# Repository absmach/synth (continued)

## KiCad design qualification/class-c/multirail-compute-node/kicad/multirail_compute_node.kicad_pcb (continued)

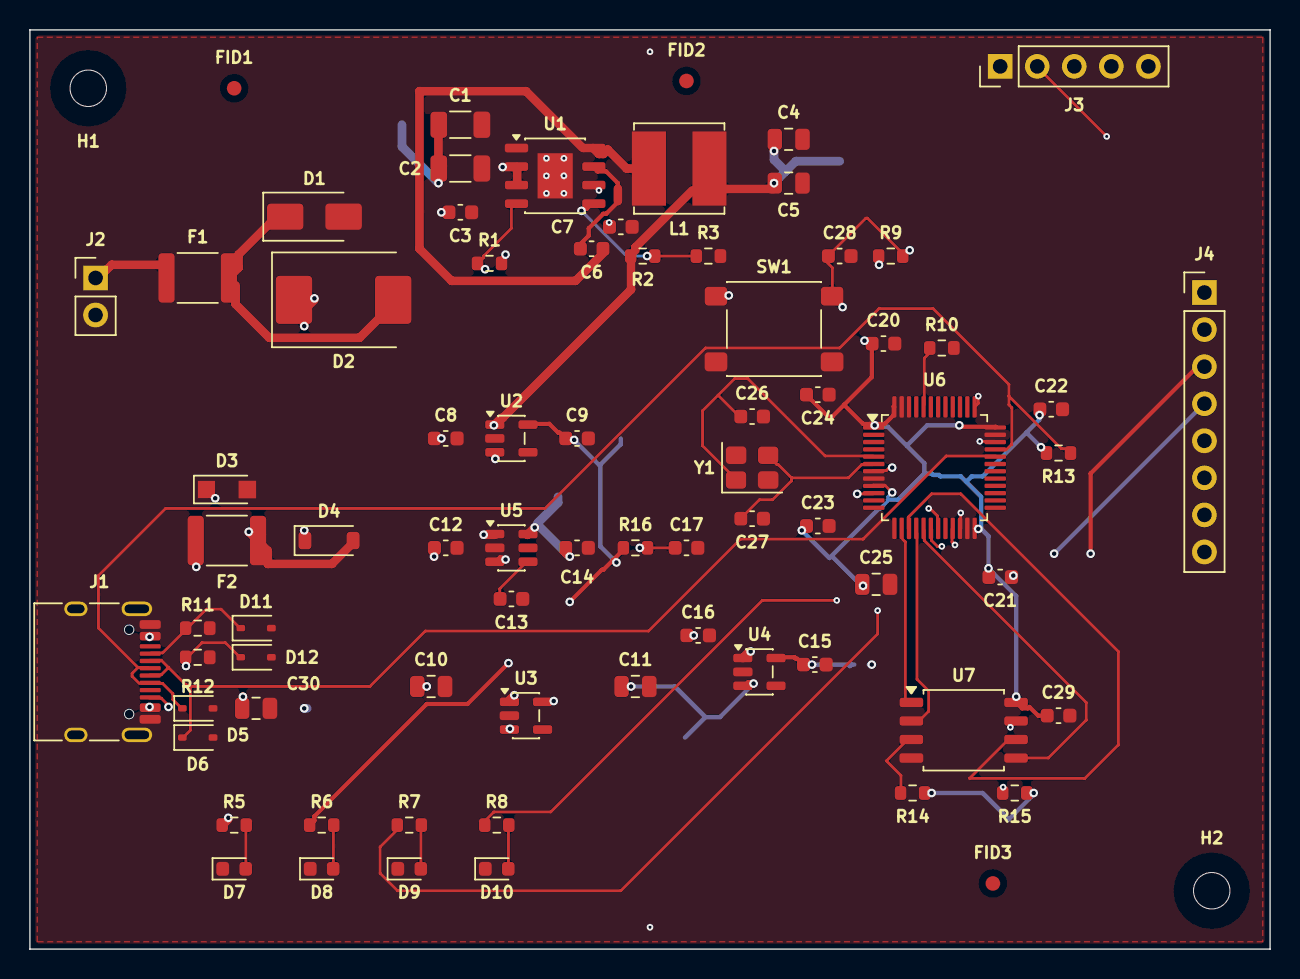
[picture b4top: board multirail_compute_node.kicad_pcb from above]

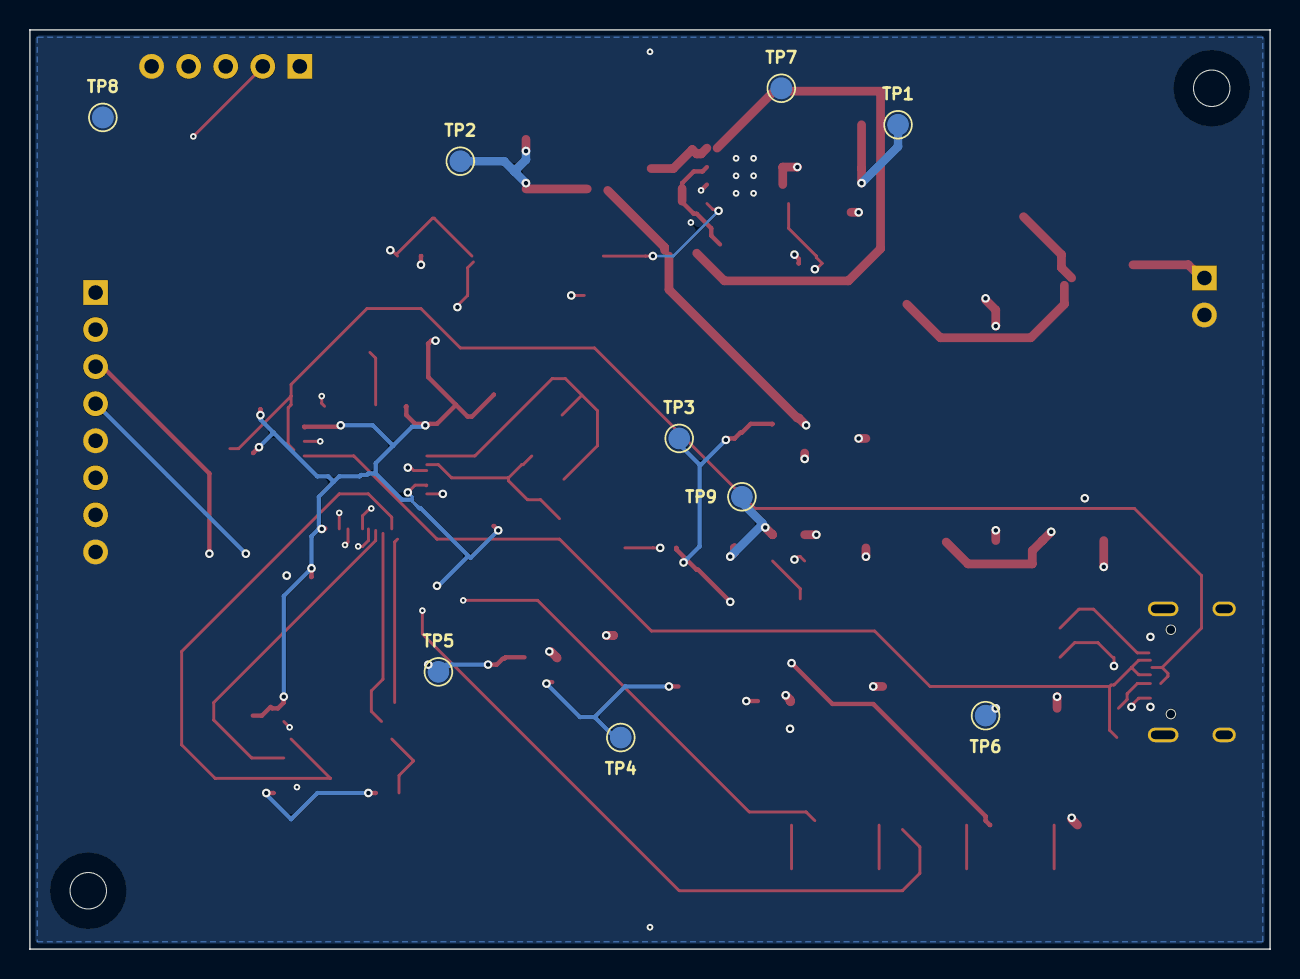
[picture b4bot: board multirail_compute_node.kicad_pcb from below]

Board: 4 copper layers, 85.0 x 63.0 mm, 85 parts (9 on the bottom side), 42 nets.

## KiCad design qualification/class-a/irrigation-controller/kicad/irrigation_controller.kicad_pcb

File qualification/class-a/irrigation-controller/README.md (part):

# Irrigation controller (Class A, case 1)

A two-zone irrigation controller powered from 12 V DC. It has an input fuse, a TVS, an ideal-diode reverse-polarity stage, an MP2307 buck to 3.3 V, an STM32G030 microcontroller, two low-side solenoid drivers, two soil probes with AC excitation, a flow-pulse input and an I2C header with an ambient light sensor and an EEPROM. The board has two copper layers, uses the JLCPCB process and measures 79.2 x 70.7 mm.

The board answers case 1 of the Class A qualification set: a mixed power, MCU and field-wiring design. It claims only what the tables below show from the board files, the measured KiCad checks and the cited datasheets. No figure is measured on hardware.

The prompt to reproduce the board is in [`PROMPT.md`](PROMPT.md), written from the finished board. The prompts the agent ran are in the history at `e0e004eb`.

## The board

### Parts

| Group                     | Parts                                                                                                                                                                                                                                                                                                      |
| ------------------------- | ---------------------------------------------------------------------------------------------------------------------------------------------------------------------------------------------------------------------------------------------------------------------------------------------------------- |
| Power input               | `J1` JST XH 2-pin supply connector; `F1` Littelfuse 1812L150/16DR resettable fuse (1.5 A hold); `D_TVS` SMAJ13A (13.0 V standoff, 21.5 V clamp at 18.6 A)                                                                                                                                                  |
| Ideal-diode stage         | `U_IDEAL` Texas Instruments LM74700-Q1 (SOT-23-6) driving `Q1` Diodes DMT6007LFG (60 V, 8.5 mOhm maximum at 4.5 V gate drive); `C_VCAP` and `C_VIN` (100 nF each) at the controller; `C_BULK` (100 uF) on the output                                                                                       |
| 3.3 V buck                | `U1` MPS MP2307DN; input capacitors `C_IN1` and `C_IN2` (10 uF); inductor `L1` Bourns SRN6045TA-100M (10 uH); output capacitors `C_OUT1` and `C_OUT2` (22 uF); feedback divider `R_FBT` 26.1 k and `R_FBB` 10 k; compensation `R_COMP` 5.6 k and `C_COMP` 4.7 nF; soft-start `C_SS`; enable divider `R_EN` |
| MCU                       | `U2` STMicroelectronics STM32G030K8T6 (LQFP-32); supply capacitors `C_VDD1` and `C_VDD2`; reset network `R_NRST`, `C_NRST` and the tactile switch `SW_RESET`; 5-pin SWD header `J_SWD`                                                                                                                     |
| MCU clock                 | 32.768 kHz LSE crystal `Y1` Epson FC-135 32.7680KF-AG0 (7 pF load) with `C_X1` and `C_X2` (4.3 pF); HSI16 is the system clock, because the LQFP-32 has no HSE crystal oscillator                                                                                                                           |
| Valves 1 and 2            | Per valve: a JST XH 2-pin connector (`J_VALVE1`, `J_VALVE2`); a low-side AO3400A N-MOSFET (`Q_V1`, `Q_V2`) with a 100 ohm gate resistor and a 100 k pull-down; a 1N5819HW flyback diode (`D_FLY1`, `D_FLY2`); an RC snubber (100 ohm, 10 nF)                                                               |
| Valve short-circuit sense | Per valve: a 0.1 ohm shunt (`R_SH1`, `R_SH2`) in the MOSFET source, read on `PA1` and `PA0` through 1 k and 10 nF (`R_IS`, `C_IS`)                                                                                                                                                                         |
| Soil probes 1 and 2       | Per probe: a JST PH 3-pin connector (`J_SOIL1`, `J_SOIL2`); AC excitation from two GPIOs through 10 k resistors (`R_S1`, `R_D1`, `R_S2`, `R_D2`); both probe nodes sampled through 1 k and 10 nF filters                                                                                                   |
| Flow input                | `J_FLOW` JST PH 3-pin; pull-up `R_FPU`; series resistor `R_FS`; 3.3 V zener `D_FZ` that clamps the pulse input; filter `C_FL`                                                                                                                                                                              |
| I2C                       | `J_I2C` JST PH 4-pin; 4.7 k pull-ups `R_SDA` and `R_SCL`; `U4` Broadcom APDS-9301 ambient light sensor and `U5` Microchip 24LC256 EEPROM, each with a 100 nF capacitor                                                                                                                                     |
| Humidity sensor           | None on the board. A breakout attaches to the I2C header at address 0x44.                                                                                                                                                                                                                                  |
| Field-wiring protection   | PRTR5V0U2X ESD arrays at the soil and I2C connectors (`D_ESD_S1`, `D_ESD_S2`, `D_ESD_I2C`); SMAJ15A TVS on the flow input (`D_ESD_FL`)                                                                                                                                                                     |
| Indicators                | `D_PWR` green (Lite-On LTST-C190KGKT); `D_VALVE` and `D_N1` amber (KENTO KT-0603Y); each with a series resistor                                                                                                                                                                                            |
| Test points               | `TP_VIN`, `TP_12V`, `TP_3V3`, `TP_GND`, `TP_NRST`, `TP_SWDIO`, `TP_SWCLK`, `TP_SDA`, `TP_SCL`, `TP_FLOW`, `TP_SOIL1`, `TP_SOIL2`, `TP_V1`, `TP_V2`, `TP_N1`, `TP_N2`, all on the bottom side of the board |
| Mechanical                | Four M2.5 mounting holes `H1` to `H4`, one in each corner, each 4.0 mm from its two board edges                                                                                                                                                                                                                                                  |

### Layout

| Item                    | Value                                                                                                                                                                                                     |
| ----------------------- | --------------------------------------------------------------------------------------------------------------------------------------------------------------------------------------------------------- |
| Outline                 | 79.2 x 70.7 mm                                                                                                                                                                                            |
| Copper layers           | 2                                                                                                                                                                                                         |
| Stackup                 | 1.6 mm board thickness; JLCPCB process; no layer stackup is defined in the board file                                                                                                                     |
| Parts in the BOM        | 107 lines: 87 parts and 20 board features (4 mounting holes, 16 test points)                                                                                                                              |
| Parts placed in the CPL | 87                                                                                                                                                                                                        |
| Nets                    | 51                                                                                                                                                                                                        |
| Track segments          | 629                                                                                                                                                                                                       |
| Vias                    | 117: 1 of 0.46/0.2 mm, 109 of 0.6/0.2 mm and 7 of 0.6/0.3 mm                                                                                                                                                                                                       |
| Track length            | 1644.7 mm                                                                                                                                                                                                 |
| Zones and planes        | GND pour on F.Cu and on B.Cu; four keepout zones at the screw heads of `H1` to `H4` on both layers                                                                                                        |
| Fab package             | `fab/gerbers.zip` (copper, mask, paste, silkscreen, edge cuts, PTH and NPTH drill files and maps, job file), `fab/bom.csv`, `fab/cpl.csv`; STEP model in `models/`; images and schematic PDF in `images/` |
| 3D models               | `models/` holds the STEP body of every part the board references and the board model `irrigation_controller.step`. The board file reaches them by the relative path `${KIPRJMOD}/../models/`. Mounting holes and fiducials have no body. A part that KiCad's library has no model for is a simplified box of its envelope. |
| Schematic               | `images/schematic.pdf`: vector pages, one per sheet, plotted by `kicad-cli sch export pdf`. |

### Checks

| Check                              | Result                               | Notes                                                                                         |
| ---------------------------------- | ------------------------------------ | --------------------------------------------------------------------------------------------- |
| KiCad DRC (10.0.8, --refill-zones) | 0 errors, 0 unconnected, 7 warnings  | 6 `silk_over_copper`, 1 `silk_overlap`                                                        |
| KiCad ERC (10.0.8)                 | 0 errors, 0 unconnected, 28 warnings | 27 `lib_symbol_issues` (library symbol and footprint-link warnings), 1 `label_multiple_wires` |

### Design figures

| Area             | Item                       | Value                                                                                                                                                                                  | Basis                                      |
| ---------------- | -------------------------- | -------------------------------------------------------------------------------------------------------------------------------------------------------------------------------------- | ------------------------------------------ |
| Power            | Supply range               | 12 V +/-5 % (10.8 to 12.6 V)                                                                                                                                                           | Stated design assumption                   |
| Power            | Load budget                | 1.18 A at 12 V: two valves 1.0 A, buck input and flow sensor 0.18 A. 1.25 A at 13.0 V.                                                                                                 | Calculated                                 |
| Power            | Buck compensation          | `R_COMP` 5.6 k and `C_COMP` 4.7 nF put the crossover at 24 kHz (44 uF output) to 34 kHz (about 31 uF after DC-bias derating). This is 0.07 to 0.10 of the 340 kHz switching frequency. | Calculated; MP2307 datasheet               |
| Power            | Ideal-diode capacitors     | `C_VCAP` 100 nF (at least 0.1 uF and 10 x the 2.09 nF Ciss of `Q1`); `C_VIN` 100 nF (at least 22 nF); `C_BULK` 100 uF (at least 100 nF)                                                | LM74700-Q1 and DMT6007LFG datasheets       |
| Power            | `Q1` conduction            | 10 mV drop and 12 mW at 1.18 A                                                                                                                                                         | Calculated from the 8.5 mOhm maximum       |
| Protection       | Surge                      | At most 14 A peak (10/1000 us), 75 % of the SMAJ13A's 18.6 A rating                                                                                                                    | SMAJ13A datasheet; calculated              |
| Protection       | Open-circuit surge covered | 21.5 V + 14 A x R_source: 35.5 V at 1 ohm, 49.5 V at 2 ohm                                                                                                                             | Calculated                                 |
| Protection       | TVS standoff               | 12.6 V is 0.4 V (3.2 %) below the 13.0 V standoff; leakage at most 1 uA there; breakdown 14.40 V minimum at 1 mA                                                                       | SMAJ13A datasheet                          |
| Protection       | Clamp margin, `U1`         | At 21.5 V: 1.5 V below the MP2307's 23 V recommended input; 4.5 V below its 26 V absolute maximum                                                                                      | MP2307 datasheet; calculated               |
| Protection       | Clamp margin, `U_IDEAL`    | At 21.5 V: 43.5 V below its 65 V maximum                                                                                                                                               | LM74700-Q1 datasheet; calculated           |
| Protection       | Clamp margin, `Q1`         | At 21.5 V: 38.5 V below its 60 V rating                                                                                                                                                | DMT6007LFG datasheet; calculated           |
| Protection       | Clamp margin, capacitors   | At 21.5 V: `C_BULK`, `C_IN1`, `C_IN2` are 3.5 V below their 25 V rating                                                                                                                | `fab/bom.csv` ratings; calculated          |
| Protection       | Valve short circuit        | `R_SH1`, `R_SH2` (0.1 ohm, 1 W) give 50 mV at 0.5 A and 0.15 V at the 1.5 A fuse hold. Firmware trips at 0.1 V (1.0 A).                                                                | Calculated                                 |
| Protection       | Flow input clamp           | `D_FZ` 3.3 V zener behind `R_FS` 2.2 k: 4.4 mA and 14 mW at 13.0 V, in a 500 mW part                                                                                                   | Calculated                                 |
| Thermal          | Fuse derating              | `F1` holds 1.5 A at 20 C, 1.25 A at 40 C, 1.10 A at 50 C and 0.60 A at 85 C                                                                                                            | 1812L150/16DR datasheet                    |
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
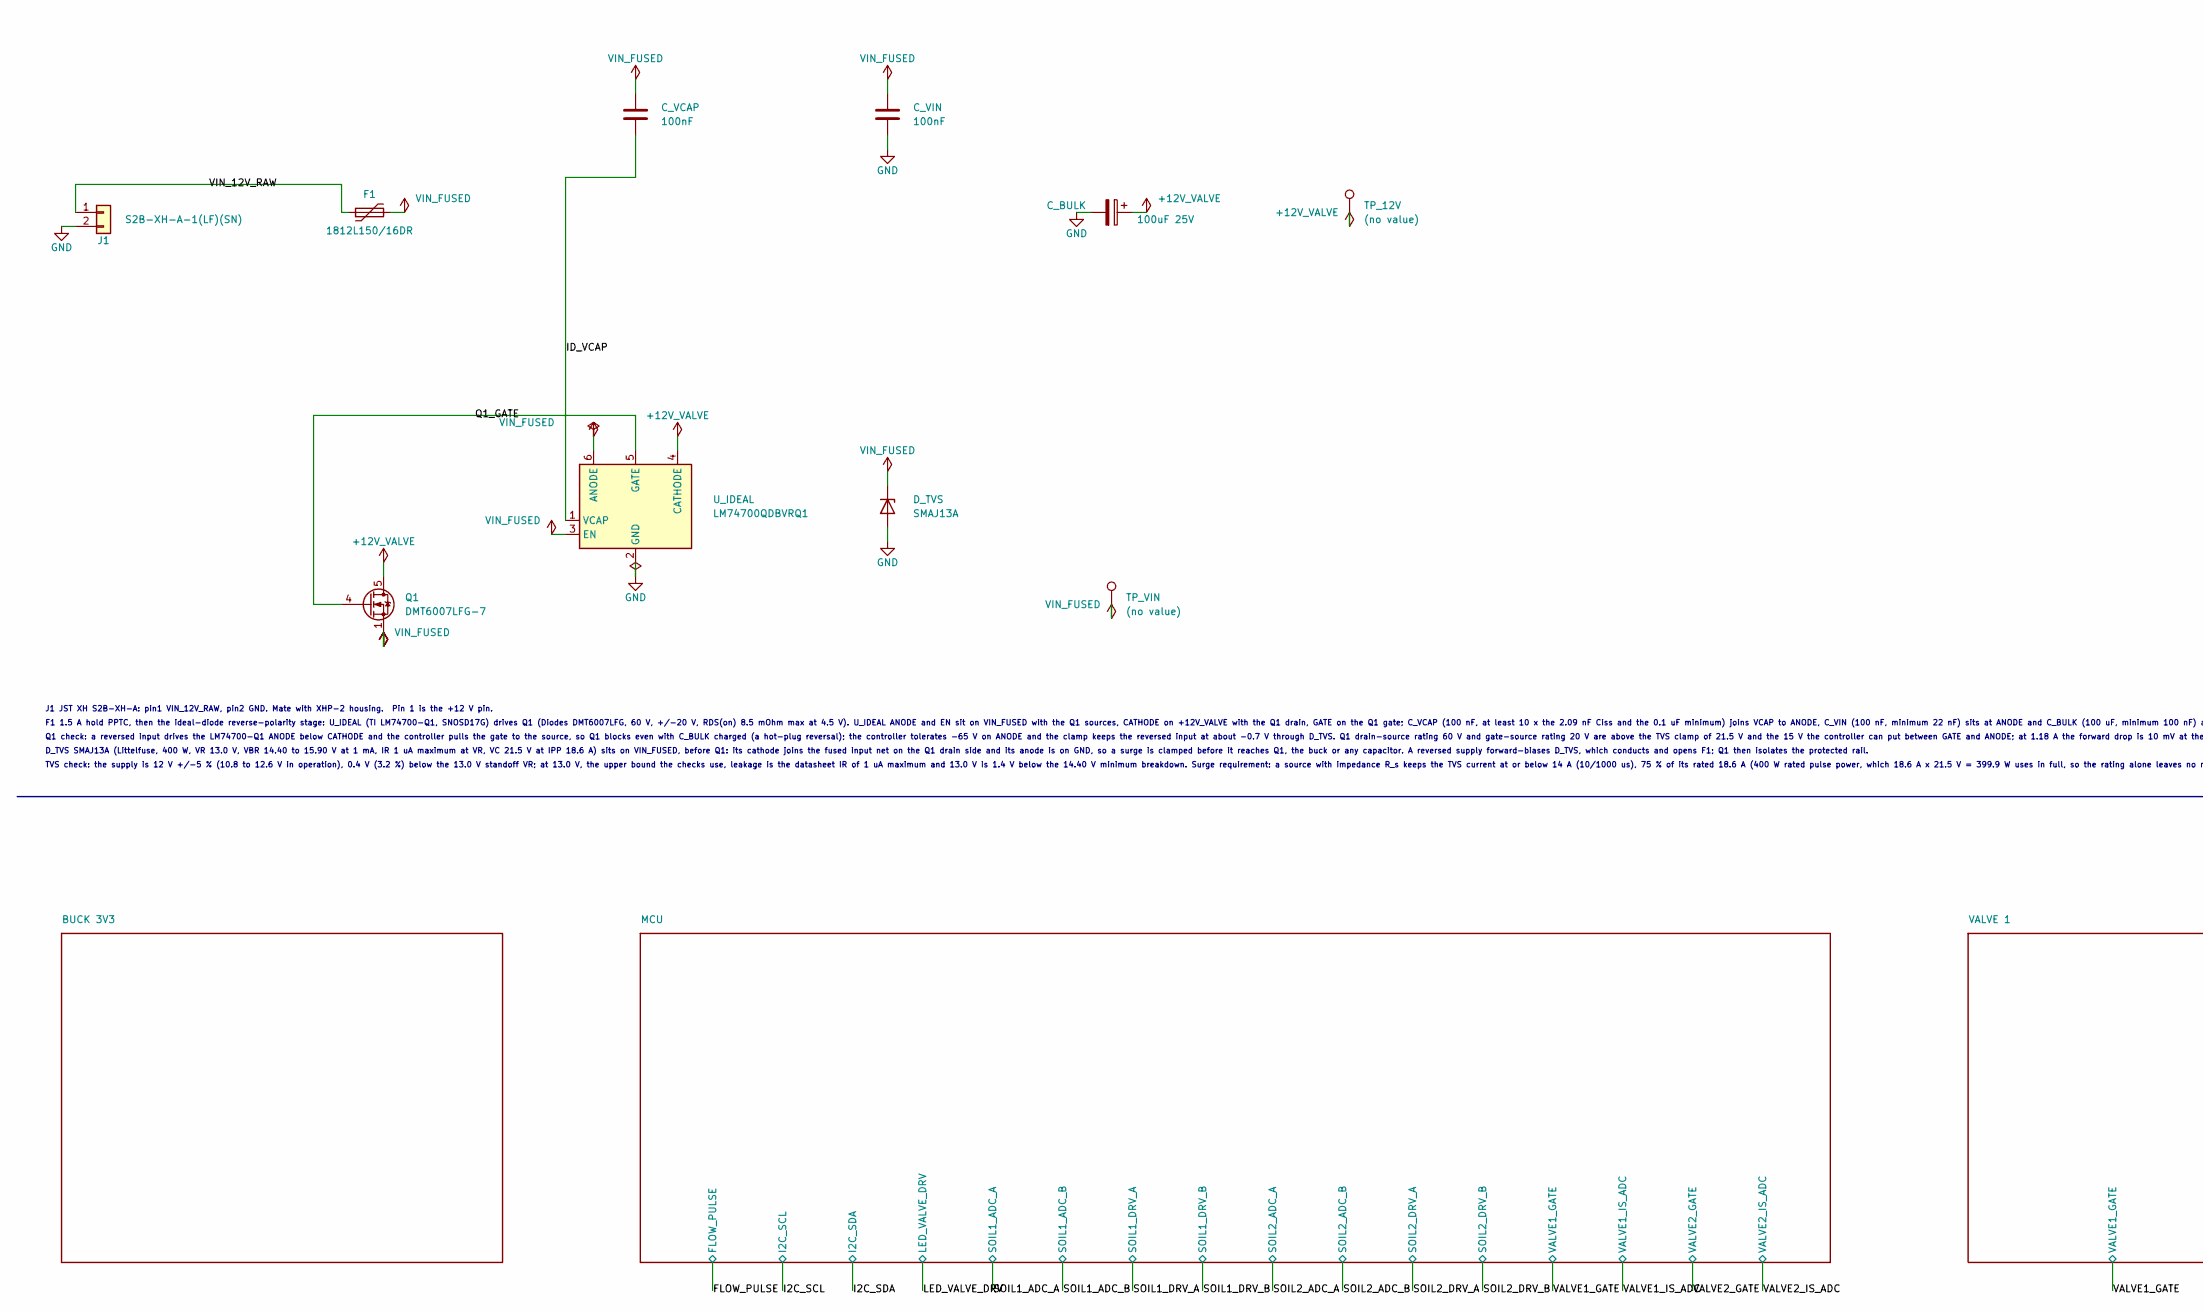
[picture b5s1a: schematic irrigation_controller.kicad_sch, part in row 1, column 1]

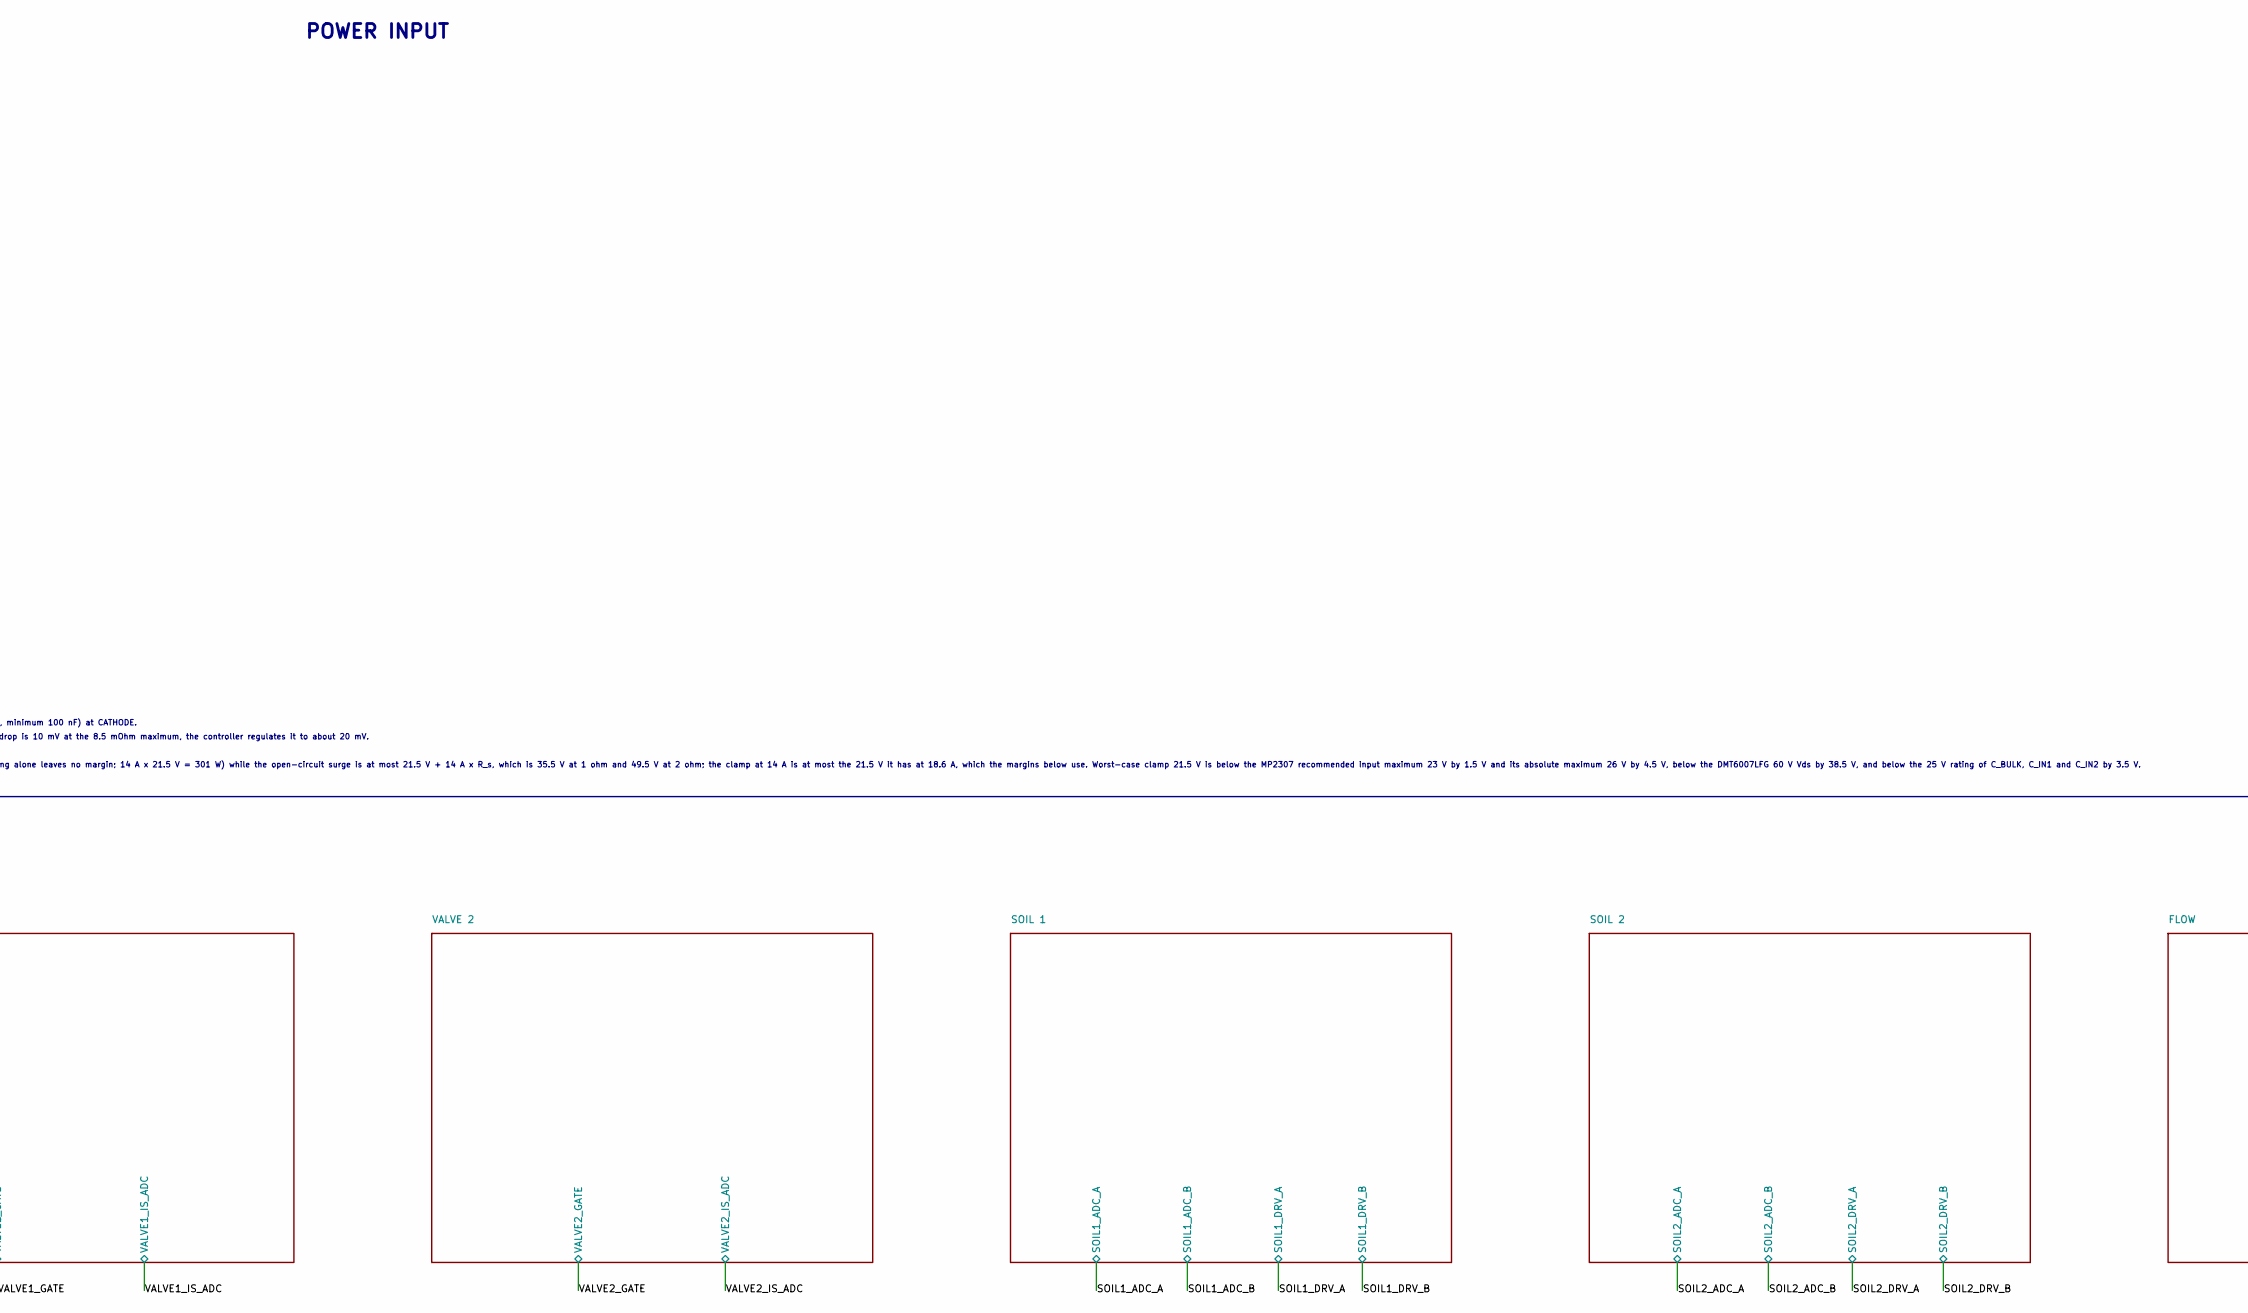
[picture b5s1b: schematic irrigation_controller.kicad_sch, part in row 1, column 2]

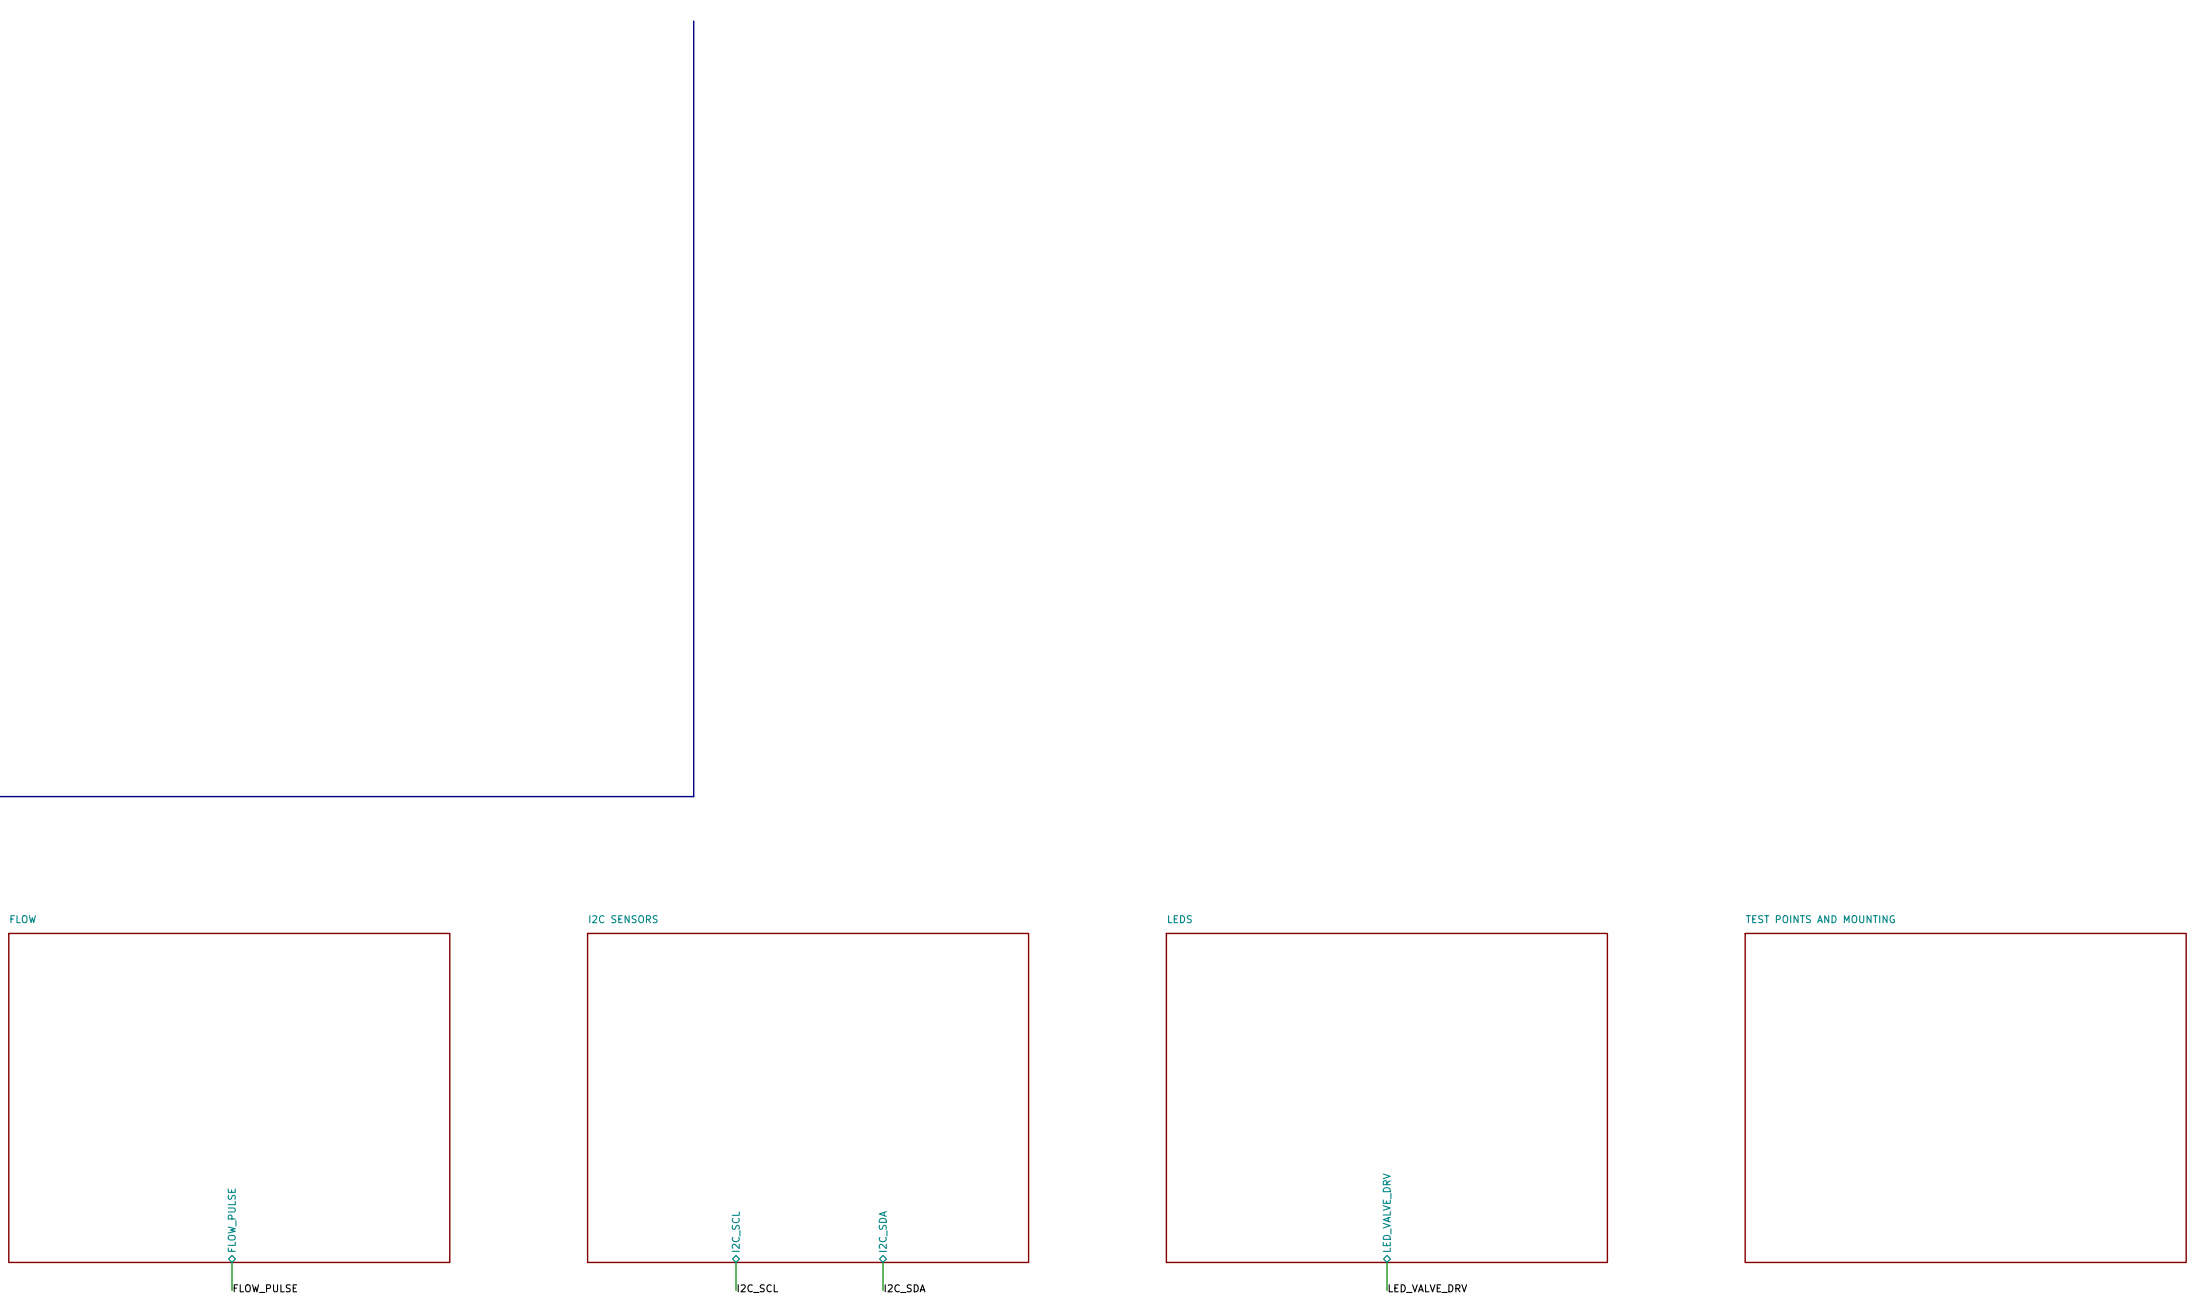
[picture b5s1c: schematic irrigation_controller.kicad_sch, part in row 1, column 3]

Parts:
C_BULK: 100uF 25V; CP_Radial_D6.3mm_P2.50mm
C_VCAP: 100nF; C_0603_1608Metric
C_VIN: 100nF; C_0603_1608Metric
D_TVS: SMAJ13A; D_SMA; MPN SMAJ13A
F1: 1812L150/16DR; Fuse_1812_4532Metric; MPN 1812L150/16DR; LCSC C207070
J1: S2B-XH-A-1(LF)(SN); JST_XH_S2B-XH-A-1_1x02_P2.50mm_Horizontal; MPN S2B-XH-A-1(LF)(SN); LCSC C163035
Q1: DMT6007LFG-7; Diodes_PowerDI3333-8; MPN DMT6007LFG-7; LCSC C2802568
TP_12V: (no value); TestPoint_Pad_D1.5mm
TP_VIN: (no value); TestPoint_Pad_D1.5mm
U_IDEAL: LM74700QDBVRQ1; SOT-23-6; MPN LM74700QDBVRQ1; LCSC C2941042

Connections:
+12V_VALVE: C_BULK.1, Q1.5 (D), TP_12V.1, U_IDEAL.4 (CATHODE); also elsewhere on the board
GND: C_BULK.2, C_VIN.2, D_TVS.2 (A), J1.2, U_IDEAL.2 (GND); also elsewhere on the board
ID_VCAP: C_VCAP.1, U_IDEAL.1 (VCAP)
Q1_GATE: Q1.4 (G), U_IDEAL.5 (GATE)
VIN_12V_RAW: F1.1, J1.1
VIN_FUSED: C_VCAP.2, C_VIN.1, D_TVS.1 (K), F1.2, Q1.1 (S), Q1.2 (S), Q1.3 (S), TP_VIN.1, U_IDEAL.3 (EN), U_IDEAL.6 (ANODE)

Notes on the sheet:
POWER INPUT
J1 JST XH S2B-XH-A: pin1 VIN_12V_RAW, pin2 GND. Mate with XHP-2 housing. Pin 1 is the +12 V pin.
F1 1.5 A hold PPTC, then the ideal-diode reverse-polarity stage: U_IDEAL (TI LM74700-Q1, SNOSD17G) drives Q1 (Diodes DMT6007LFG, 60 V, +/-20 V, RDS(on) 8.5 mOhm max at 4.5 V). U_IDEAL ANODE and EN sit on VIN_FUSED with the Q1 sources, CATHODE on +12V_VALVE with the Q1 drain, GATE on the Q1 gate; C_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
Q1 check: a reversed input drives the LM74700-Q1 ANODE below CATHODE and the controller pulls the gate to the source, so Q1 blocks even with C_BULK charged (a hot-plug reversal); the controller tolerates -65 V on ANODE and the clamp keeps the reversed input at about -0.7 V through D_TVS. Q1 drain-s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
D_TVS SMAJ13A (Littelfuse, 400 W, VR 13.0 V, VBR 14.40 to 15.90 V at 1 mA, IR 1 uA maximum at VR, VC 21.5 V at IPP 18.6 A) sits on VIN_FUSED, before Q1: its cathode joins the fused input net on the Q1 drain side and its anode is on GND, so a surge is clamped before it reaches Q1, the buck or any ca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
TVS check: the supply is 12 V +/-5 % (10.8 to 12.6 V in operation), 0.4 V (3.2 %) below the 13.0 V standoff VR; at 13.0 V, the upper bound the checks use, leakage is the datasheet IR of 1 uA maximum and 13.0 V is 1.4 V below the 14.40 V minimum breakdown. Surge requirement: a source with impedance 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

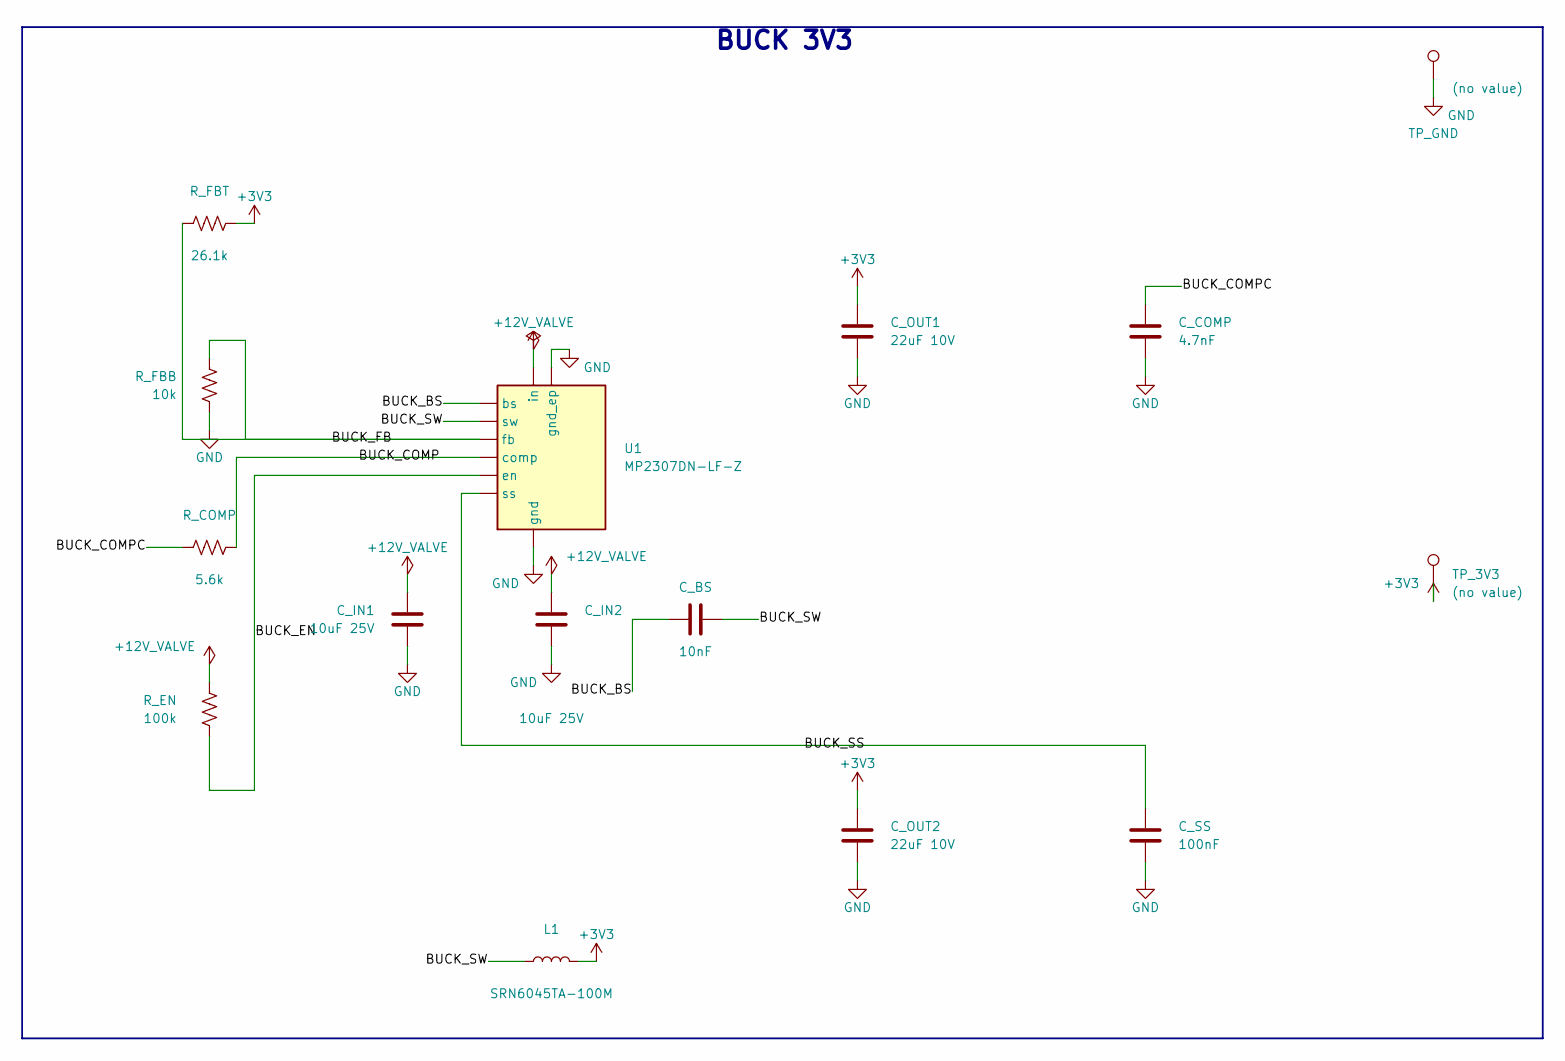
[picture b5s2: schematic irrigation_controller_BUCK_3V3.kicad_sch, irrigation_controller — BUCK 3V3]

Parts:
C_BS: 10nF; C_0603_1608Metric
C_COMP: 4.7nF; C_0603_1608Metric
C_IN1, C_IN2: 10uF 25V; C_0805_2012Metric
C_OUT1, C_OUT2: 22uF 10V; C_1206_3216Metric
C_SS: 100nF; C_0603_1608Metric
L1: SRN6045TA-100M; L_Bourns_SRN6045TA; MPN SRN6045TA-100M
R_COMP: 5.6k; R_0603_1608Metric
R_EN: 100k; R_0603_1608Metric
R_FBB: 10k; R_0603_1608Metric
R_FBT: 26.1k; R_0603_1608Metric
TP_3V3: (no value); TestPoint_Pad_D1.5mm
TP_GND: (no value); TestPoint_Pad_D1.5mm
U1: MP2307DN-LF-Z; SOIC-8-1EP_3.9x4.9mm_P1.27mm_EP2.41x3.3mm; MPN MP2307DN-LF-Z; LCSC C18921

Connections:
+3V3: C_OUT1.1, C_OUT2.1, L1.2, R_FBT.1, TP_3V3.1; also elsewhere on the board
+12V_VALVE: C_IN1.1, C_IN2.1, R_EN.1, U1.2 (in); also elsewhere on the board
BUCK_BS: C_BS.1, U1.1 (bs)
BUCK_COMP: R_COMP.1, U1.6 (comp)
BUCK_COMPC: C_COMP.1, R_COMP.2
BUCK_EN: R_EN.2, U1.7 (en)
BUCK_FB: R_FBB.1, R_FBT.2, U1.5 (fb)
BUCK_SS: C_SS.1, U1.8 (ss)
BUCK_SW: C_BS.2, L1.1, U1.3 (sw)
GND: C_COMP.2, C_IN1.2, C_IN2.2, C_OUT1.2, C_OUT2.2, C_SS.2, R_FBB.2, TP_GND.1, U1.4 (gnd), U1.9 (gnd_ep); also elsewhere on the board

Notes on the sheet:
BUCK 3V3

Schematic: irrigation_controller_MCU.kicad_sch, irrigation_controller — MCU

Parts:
C_NRST: 100nF; C_0603_1608Metric
C_VDD1: 100nF; C_0603_1608Metric
C_VDD2: 4.7uF; C_0805_2012Metric
C_X1, C_X2: 4.3pF; C_0603_1608Metric
J_SWD: M20-9990546; PinHeader_1x05_P2.54mm_Vertical; MPN M20-9990546; LCSC C3328227
R_NRST: 10k; R_0603_1608Metric
SW_RESET: PTS645SM43SMTR92 LFS; SW_SPST_PTS645Sx43SMTR92; MPN PTS645SM43SMTR92 LFS; LCSC C221880
TP_NRST: (no value); TestPoint_Pad_D1.5mm
TP_SWCLK: (no value); TestPoint_Pad_D1.5mm
TP_SWDIO: (no value); TestPoint_Pad_D1.5mm
U2: (no value); LQFP-32_7x7mm_P0.8mm
Y1: FC-135 32.7680KF-AG0; Crystal_SMD_3215-2Pin_3.2x1.5mm; MPN FC-135 32.7680KF-AG0; LCSC C7275974

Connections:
+3V3: C_VDD1.1, C_VDD2.1, J_SWD.1, R_NRST.1, U2.4 (VDD); also elsewhere on the board
FLOW_PULSE: U2.13 (PA6); also elsewhere on the board
GND: C_NRST.2, C_VDD1.2, C_VDD2.2, C_X1.2, C_X2.2, J_SWD.3, SW_RESET.2, U2.5 (VSS); also elsewhere on the board
I2C_SCL: U2.30 (PB6); also elsewhere on the board
I2C_SDA: U2.31 (PB7); also elsewhere on the board
LED_VALVE_DRV: U2.14 (PA7); also elsewhere on the board
NRST: C_NRST.1, J_SWD.5, R_NRST.2, SW_RESET.1, TP_NRST.1, U2.6 (NRST)
OSC_IN: C_X1.1, U2.2 (PC14), Y1.1
OSC_OUT: C_X2.1, U2.3 (PC15), Y1.2
SOIL1_ADC_A: U2.9 (PA2); also elsewhere on the board
SOIL1_ADC_B: U2.15 (PB0); also elsewhere on the board
SOIL1_DRV_A: U2.11 (PA4); also elsewhere on the board
SOIL1_DRV_B: U2.18 (PA8); also elsewhere on the board
SOIL2_ADC_A: U2.10 (PA3); also elsewhere on the board
SOIL2_ADC_B: U2.16 (PB1); also elsewhere on the board
SOIL2_DRV_A: U2.12 (PA5); also elsewhere on the board
SOIL2_DRV_B: U2.26 (PA15); also elsewhere on the board
SWCLK: J_SWD.4, TP_SWCLK.1, U2.25 (PA14)
SWDIO: J_SWD.2, TP_SWDIO.1, U2.24 (PA13)
VALVE1_GATE: U2.27 (PB3); also elsewhere on the board
VALVE1_IS_ADC: U2.8 (PA1); also elsewhere on the board
VALVE2_GATE: U2.28 (PB4); also elsewhere on the board
VALVE2_IS_ADC: U2.7 (PA0); also elsewhere on the board

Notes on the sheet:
MCU
J_SWD pin1 +3V3, pin2 SWDIO, pin3 GND, pin4 SWCLK, pin5 NRST. No USB bootloader; program over SWD.
LSE 32.768 kHz on PC14/PC15 (OSC32_IN/OSC32_OUT): the LQFP-32 STM32G030K8 has no HSE crystal oscillator (HSE runs only in bypass mode), so the system clock is HSI16 and the crystal feeds the RTC. Crystal Epson FC-135 32.7680KF-AG0 (LCSC C7275974), CL 7 pF, R1 70 kOhm typ, C0 1.0 pF typ (Epson FC-13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
Boot: PA14 (SWCLK) is BOOT0; default option bytes boot from flash.

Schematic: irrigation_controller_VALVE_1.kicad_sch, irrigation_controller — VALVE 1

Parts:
C_IS1: 10nF; C_0603_1608Metric
C_SN1: 10nF; C_0603_1608Metric
D_FLY1: 1N5819HW-7-F; D_SOD-123; MPN 1N5819HW-7-F; LCSC C82544
J_VALVE1: S2B-XH-A-1(LF)(SN); JST_XH_S2B-XH-A-1_1x02_P2.50mm_Horizontal; MPN S2B-XH-A-1(LF)(SN); LCSC C163035
Q_V1: AO3400A; SOT-23; MPN AO3400A
R_G1: 100; R_0603_1608Metric
R_IS1: 1k; R_0603_1608Metric
R_PD1: 100k; R_0603_1608Metric
R_SH1: 0.1; R_1206_3216Metric
R_SN1: 100; R_0603_1608Metric
TP_V1: (no value); TestPoint_Pad_D1.5mm

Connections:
+12V_VALVE: D_FLY1.1 (K), J_VALVE1.1, R_SN1.1; also elsewhere on the board
GND: C_IS1.2, R_PD1.2, R_SH1.2; also elsewhere on the board
SNUB1: C_SN1.1, R_SN1.2
VALVE1_GATE: R_G1.1; also elsewhere on the board
VALVE1_GATE_Q: Q_V1.1 (G), R_G1.2, R_PD1.1
VALVE1_ISENSE: Q_V1.2 (S), R_IS1.1, R_SH1.1
VALVE1_IS_ADC: C_IS1.1, R_IS1.2; also elsewhere on the board
VALVE1_SW: C_SN1.2, D_FLY1.2 (A), J_VALVE1.2, Q_V1.3 (D), TP_V1.1

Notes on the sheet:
VALVE 1
J_VALVE1 pin1 +12V_VALVE, pin2 VALVE1_SW (low-side). Flyback cathode to +12V_VALVE.
Short-circuit sensing: R_SH1 0.1 ohm 1 W (FOJAN FRM121WFR100TM) sits in the source of Q_V1; the sensed voltage is I x 0.1 ohm, 50 mV at the 0.5 A coil current and 0.15 V at the 1.5 A hold current of F1, read on PA1 through R_IS1 1 k and C_IS1 10 nF. Firmware turns the valve off when the sensed volt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
Load: 12 V DC solenoid, coil current at most 0.5 A. AO3400A carries 0.5 A (rated far above, needs datasheet value sourcing for the exact figure), flyback diode 1N5819-class (1 A class), VALVE1_SW is class PWR12 (0.8 mm, about 8x the width a 0.5 A / 10 C rise needs).

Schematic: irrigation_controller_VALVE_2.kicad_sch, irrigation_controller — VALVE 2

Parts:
C_IS2: 10nF; C_0603_1608Metric
C_SN2: 10nF; C_0603_1608Metric
D_FLY2: 1N5819HW-7-F; D_SOD-123; MPN 1N5819HW-7-F; LCSC C82544
J_VALVE2: S2B-XH-A-1(LF)(SN); JST_XH_S2B-XH-A-1_1x02_P2.50mm_Horizontal; MPN S2B-XH-A-1(LF)(SN); LCSC C163035
Q_V2: AO3400A; SOT-23; MPN AO3400A
R_G2: 100; R_0603_1608Metric
R_IS2: 1k; R_0603_1608Metric
R_PD2: 100k; R_0603_1608Metric
R_SH2: 0.1; R_1206_3216Metric
R_SN2: 100; R_0603_1608Metric
TP_V2: (no value); TestPoint_Pad_D1.5mm

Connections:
+12V_VALVE: D_FLY2.1 (K), J_VALVE2.1, R_SN2.1; also elsewhere on the board
GND: C_IS2.2, R_PD2.2, R_SH2.2; also elsewhere on the board
SNUB2: C_SN2.1, R_SN2.2
VALVE2_GATE: R_G2.1; also elsewhere on the board
VALVE2_GATE_Q: Q_V2.1 (G), R_G2.2, R_PD2.1
VALVE2_ISENSE: Q_V2.2 (S), R_IS2.1, R_SH2.1
VALVE2_IS_ADC: C_IS2.1, R_IS2.2; also elsewhere on the board
VALVE2_SW: C_SN2.2, D_FLY2.2 (A), J_VALVE2.2, Q_V2.3 (D), TP_V2.1

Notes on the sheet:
VALVE 2
J_VALVE2 pin1 +12V_VALVE, pin2 VALVE2_SW (low-side). Flyback cathode to +12V_VALVE.
Short-circuit sensing: R_SH2 0.1 ohm 1 W (FOJAN FRM121WFR100TM) sits in the source of Q_V2; the sensed voltage is I x 0.1 ohm, 50 mV at the 0.5 A coil current and 0.15 V at the 1.5 A hold current of F1, read on PA0 through R_IS2 1 k and C_IS2 10 nF. Firmware turns the valve off when the sensed volt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
Load: 12 V DC solenoid, coil current at most 0.5 A. Same checks as valve 1: MOSFET, flyback diode and PWR12 tracks carry 0.5 A.
R_SN2 100 ohm in series with C_SN2 10 nF is an RC snubber across the valve 2 coil connector. TP_V2 probes VALVE2_SW.

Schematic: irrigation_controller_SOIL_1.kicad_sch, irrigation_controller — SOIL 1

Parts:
C_F1, C_F1B: 10nF; C_0603_1608Metric
D_ESD_S1: PRTR5V0U2X; SOT-143; MPN PRTR5V0U2X
J_SOIL1: S3B-PH-K-S(LF)(SN); JST_PH_S3B-PH-K_1x03_P2.00mm_Horizontal; MPN S3B-PH-K-S(LF)(SN); LCSC C157929
R_D1: 10k; R_0603_1608Metric
R_F1, R_F1B: 1k; R_0603_1608Metric
R_S1: 10k; R_0603_1608Metric
TP_SOIL1: (no value); TestPoint_Pad_D1.5mm

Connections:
+3V3: D_ESD_S1.4 (VCC); also elsewhere on the board
GND: C_F1.2, C_F1B.2, D_ESD_S1.1 (GND), J_SOIL1.3; also elsewhere on the board
SOIL1_A: D_ESD_S1.2 (I/O1), J_SOIL1.1, R_F1.1, R_S1.2
SOIL1_ADC_A: C_F1.1, R_F1.2, TP_SOIL1.1; also elsewhere on the board
SOIL1_ADC_B: C_F1B.1, R_F1B.2; also elsewhere on the board
SOIL1_B: D_ESD_S1.3 (I/O2), J_SOIL1.2, R_D1.2, R_F1B.1
SOIL1_DRV_A: R_S1.1; also elsewhere on the board
SOIL1_DRV_B: R_D1.1; also elsewhere on the board

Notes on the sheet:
SOIL 1
J_SOIL1 pin1 and pin2 are the probe, pin3 GND. AC excitation: the probe is driven with alternating polarity from two GPIOs through R_S1 and R_D1 (10 k each), so it never sees DC. Firmware: in each phase both nodes are sampled (SOIL1_ADC_A and SOIL1_ADC_B) with one pin driven high and the other low;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

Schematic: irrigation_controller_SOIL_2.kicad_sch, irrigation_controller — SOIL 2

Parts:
C_F2, C_F2B: 10nF; C_0603_1608Metric
D_ESD_S2: PRTR5V0U2X; SOT-143; MPN PRTR5V0U2X
J_SOIL2: S3B-PH-K-S(LF)(SN); JST_PH_S3B-PH-K_1x03_P2.00mm_Horizontal; MPN S3B-PH-K-S(LF)(SN); LCSC C157929
R_D2: 10k; R_0603_1608Metric
R_F2, R_F2B: 1k; R_0603_1608Metric
R_S2: 10k; R_0603_1608Metric
TP_SOIL2: (no value); TestPoint_Pad_D1.5mm

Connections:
+3V3: D_ESD_S2.4 (VCC); also elsewhere on the board
GND: C_F2.2, C_F2B.2, D_ESD_S2.1 (GND), J_SOIL2.3; also elsewhere on the board
SOIL2_A: D_ESD_S2.2 (I/O1), J_SOIL2.1, R_F2.1, R_S2.2
SOIL2_ADC_A: C_F2.1, R_F2.2, TP_SOIL2.1; also elsewhere on the board
SOIL2_ADC_B: C_F2B.1, R_F2B.2; also elsewhere on the board
SOIL2_B: D_ESD_S2.3 (I/O2), J_SOIL2.2, R_D2.2, R_F2B.1
SOIL2_DRV_A: R_S2.1; also elsewhere on the board
SOIL2_DRV_B: R_D2.1; also elsewhere on the board

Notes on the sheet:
SOIL 2
J_SOIL2 pin1 and pin2 are the probe, pin3 GND. AC excitation: the probe is driven with alternating polarity from two GPIOs through R_S2 and R_D2 (10 k each), so it never sees DC. Firmware: in each phase both nodes are sampled (SOIL2_ADC_A and SOIL2_ADC_B) with one pin driven high and the other low;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

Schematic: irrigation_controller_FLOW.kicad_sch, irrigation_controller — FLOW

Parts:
C_FL: 10nF; C_0603_1608Metric
D_ESD_FL: SMAJ15A; D_SMA; MPN SMAJ15A
D_FZ: (no value); D_SOD-123
J_FLOW: S3B-PH-K-S(LF)(SN); JST_PH_S3B-PH-K_1x03_P2.00mm_Horizontal; MPN S3B-PH-K-S(LF)(SN); LCSC C157929
R_FPU: 10k; R_0603_1608Metric
R_FS: 2.2k; R_0603_1608Metric
TP_FLOW: (no value); TestPoint_Pad_D1.5mm

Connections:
+3V3: R_FPU.1; also elsewhere on the board
+12V_VALVE: J_FLOW.1; also elsewhere on the board
FLOW_IN: D_ESD_FL.1 (K), J_FLOW.3, R_FPU.2, R_FS.1
FLOW_PULSE: C_FL.1, D_FZ.1 (K), R_FS.2, TP_FLOW.1; also elsewhere on the board
GND: C_FL.2, D_ESD_FL.2 (A), D_FZ.2 (A), J_FLOW.2; also elsewhere on the board

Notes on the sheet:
FLOW
J_FLOW pin1 +12V_VALVE sensor supply, pin2 GND, pin3 pulse. Open-collector assumed; 3.3 V zener D_FZ (cathode on FLOW_PULSE, anode on GND) behind R_FS 2.2 k clamps a push-pull output to the STM32G030 input range. Current at a 13.0 V sensor output: (13.0 - 3.3) / 2.2 k = 4.41 mA (12 V: 3.95 mA), abo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

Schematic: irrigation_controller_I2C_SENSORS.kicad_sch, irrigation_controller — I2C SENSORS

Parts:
C_U4, C_U5: 100nF; C_0603_1608Metric
D_ESD_I2C: PRTR5V0U2X; SOT-143; MPN PRTR5V0U2X
J_I2C: S4B-PH-K-S(LF)(SN); JST_PH_S4B-PH-K_1x04_P2.00mm_Horizontal; MPN S4B-PH-K-S(LF)(SN); LCSC C157926
R_SCL: 4.7k; R_0603_1608Metric
R_SDA: 4.7k; R_0603_1608Metric
TP_SCL: (no value); TestPoint_Pad_D1.5mm
TP_SDA: (no value); TestPoint_Pad_D1.5mm
U4: (no value); Broadcom_APDS-9301
U5: 24LC256-I/SN; SOIC-8_3.9x4.9mm_P1.27mm; MPN 24LC256-I/SN; LCSC C411625

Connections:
+3V3: C_U4.1, C_U5.1, D_ESD_I2C.4 (VCC), J_I2C.2, R_SCL.1, R_SDA.1, U4.1 (VDD), U5.8 (VCC); also elsewhere on the board
GND: C_U4.2, C_U5.2, D_ESD_I2C.1 (GND), J_I2C.1, U4.2 (GND), U4.3 (ADR_SEL), U5.1 (A0), U5.2 (A1), U5.3 (A2), U5.4 (GND), U5.7 (WP); also elsewhere on the board
I2C_SCL: D_ESD_I2C.3 (I/O2), J_I2C.4, R_SCL.2, TP_SCL.1, U4.4 (SCL), U5.6 (SCL); also elsewhere on the board
I2C_SDA: D_ESD_I2C.2 (I/O1), J_I2C.3, R_SDA.2, TP_SDA.1, U4.5 (SDA), U5.5 (SDA); also elsewhere on the board

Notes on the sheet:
I2C SENSORS
Addresses: APDS-9301 0x29 (ADR_SEL low), 24LC256 0x50 (A2..A0 low). No collisions. An SHT30 breakout attaches to J_I2C at address 0x44, which stays free.
J_I2C pin1 GND, pin2 +3V3, pin3 SDA, pin4 SCL. 3.3 V only, no 5 V; external load <= 100 mA.
